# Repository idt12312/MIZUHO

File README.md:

# MIZUHOについて
## 概要
マイクロマウスの機体です。  

第37回全日本マイクロマウス大会のクラッシック競技フレッシュマンクラスに出場しました。  
予選を通過し、決勝では11位のタイムで完走しました。

## 使用部品

|          |                 |
|------------------|--------------------------|
| マイコン         | STM32F405RGT                |
| 6軸センサ        | MPU6500                  |
| モータドライバ   | DRV8835                  |
| フォトダイオード | SFH213FA                 |
| 赤外線LED        | VSLY5850                 |
| モーター         | Faulhaber 1717+IEH2-1024 |
| バッテリー       | Hyperion 1cel 120mA × 2  |

# 内容物
* pcb/ : kicadの基板データ
* firmware/ : stm32のファームウェア(eclipseのプロジェクトファイル)

# ファームウェアについて 
## 構成
↓の画像のような構成になっています。

[FreeRTOS](http://www.freertos.org/)を利用しています。  
上の画像の緑の色のついている部分がFreeRTOSのタスクになっています。  

## 制御の概要
だいたいこんな感じです。

## 探索アルゴリズム
[以前作ったもの](https://github.com/idt12312/MazeSolver2015)を使用しています。

# 回路について
[回路図はここからpdfダウンロードできます。](./doc/micromouse2016.pdf)

## 壁センサ
壁センサは少し工夫したので説明しておきます。  
ロ技研内での技術交流のために作成したまとめ文章も置いておくので、よかったら見てください  
[研究報告書](https://github.com/idt12312/MIZUHO/blob/master/doc/docment.pdf)  

外乱を防ぐために赤外線LEDを変調して使っています。

受光した信号は直交復調に基づいて復調しています。  
計算自体はDFTをとある周波数についてだけ計算することと同じです。  

受光した信号を

、サンプリング周波数を

とします。  
ここでは

から周波数

成分の強度を計算するとします。  

まず

を計算します。  

次に

の絶対値を計算することで  

に含まれる周波数

の振幅を得ることができます。

# 開発環境
## 基板
* 基板の外形はinventorで作成 -> dxfで出力
* 回路図・アートワークはKiCad 4.0.4-stableで作成

## STM32
* コンパイラ : GCC 4.9.3 (arm-none-eabi)
* デバッガ : GDB 7.8.0.20150604-cvs (arm-none-eabi)
* OpenOCD 0.9.0
* IDE : Eclipse
  * CDT
  * GNU ARM Eclipse plugin
* eclipseのプロジェクトの雛形はGNU ARM Eclipse pluginから自動生成されるものを使用
* STM32のStandard Peripheral Libraryを使用

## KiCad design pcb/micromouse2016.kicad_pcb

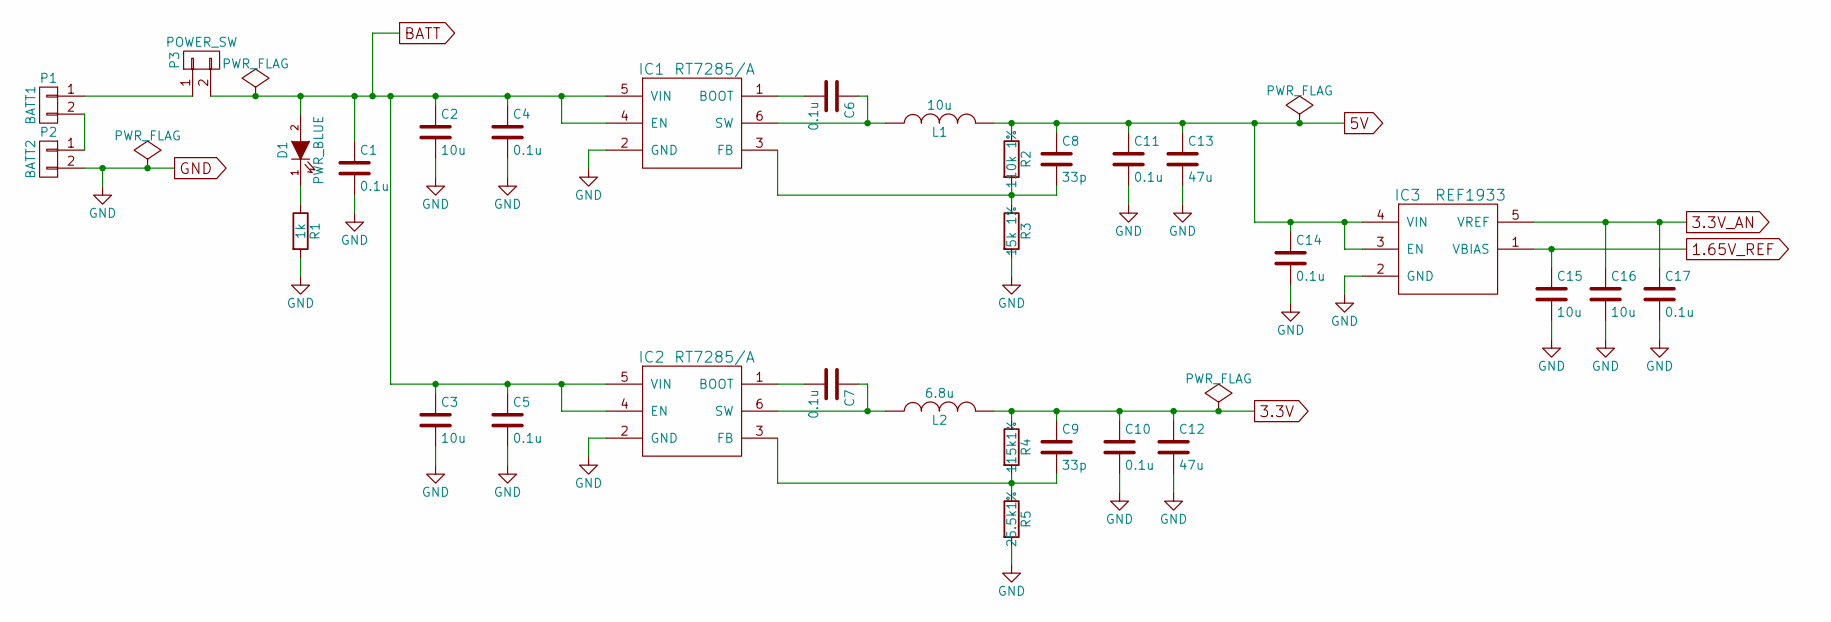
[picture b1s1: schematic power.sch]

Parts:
C1, C4, C5, C6, C7, C10, C11, C14, C17: 0.1u; C_0603
C2, C3, C15, C16: 10u; C_0603
C8, C9: 33p; C_0603
C12, C13: 47u; C_1206
D1: PWR_BLUE; LED_0805
IC1, IC2: RT7285/A; SOT-23-6
IC3: REF1933; SOT-23-5
L1: 10u; R_0805
L2: 6.8u; R_0805
P1: BATT1; JST_PH_B2B-PH-K_02x2.00mm_Straight
P2: BATT2; JST_PH_B2B-PH-K_02x2.00mm_Straight
P3: POWER_SW; Pin_Header_Straight_1x02
R1: 1k; R_0603
R2: 110k 1%; R_0603
R3: 15k 1%; R_0603
R4: 115k1%; R_0603
R5: 25.5k1%; R_0603

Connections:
1.65V_REF: C15.1, IC3.1 (VBIAS); also elsewhere on the board
3.3V: C9.1, C10.1, C12.1, L2.2, R4.1; also elsewhere on the board
3.3V_AN: C16.1, C17.1, IC3.5 (VREF); also elsewhere on the board
5V: C8.1, C11.1, C13.1, C14.1, IC3.3 (EN), IC3.4 (VIN), L1.2, R2.1; also elsewhere on the board
BATT: C1.1, C2.1, C3.1, C4.1, C5.1, D1.2 (A), IC1.4 (EN), IC1.5 (VIN), IC2.4 (EN), IC2.5 (VIN), P3.2; also elsewhere on the board
GND: C1.2, C2.2, C3.2, C4.2, C5.2, C10.2, C11.2, C12.2, C13.2, C14.2, C15.2, C16.2, C17.2, IC1.2 (GND), IC2.2 (GND), IC3.2 (GND), P2.2, R1.2, R3.2, R5.2; also elsewhere on the board
unnamed: C6.1, IC1.6 (SW), L1.1
unnamed: C6.2, IC1.1 (BOOT)
unnamed: C7.1, IC2.6 (SW), L2.1
unnamed: C7.2, IC2.1 (BOOT)
unnamed: C8.2, IC1.3 (FB), R2.2, R3.1
unnamed: C9.2, IC2.3 (FB), R4.2, R5.1
unnamed: D1.1 (K), R1.1
unnamed: P1.1, P3.1
unnamed: P1.2, P2.1

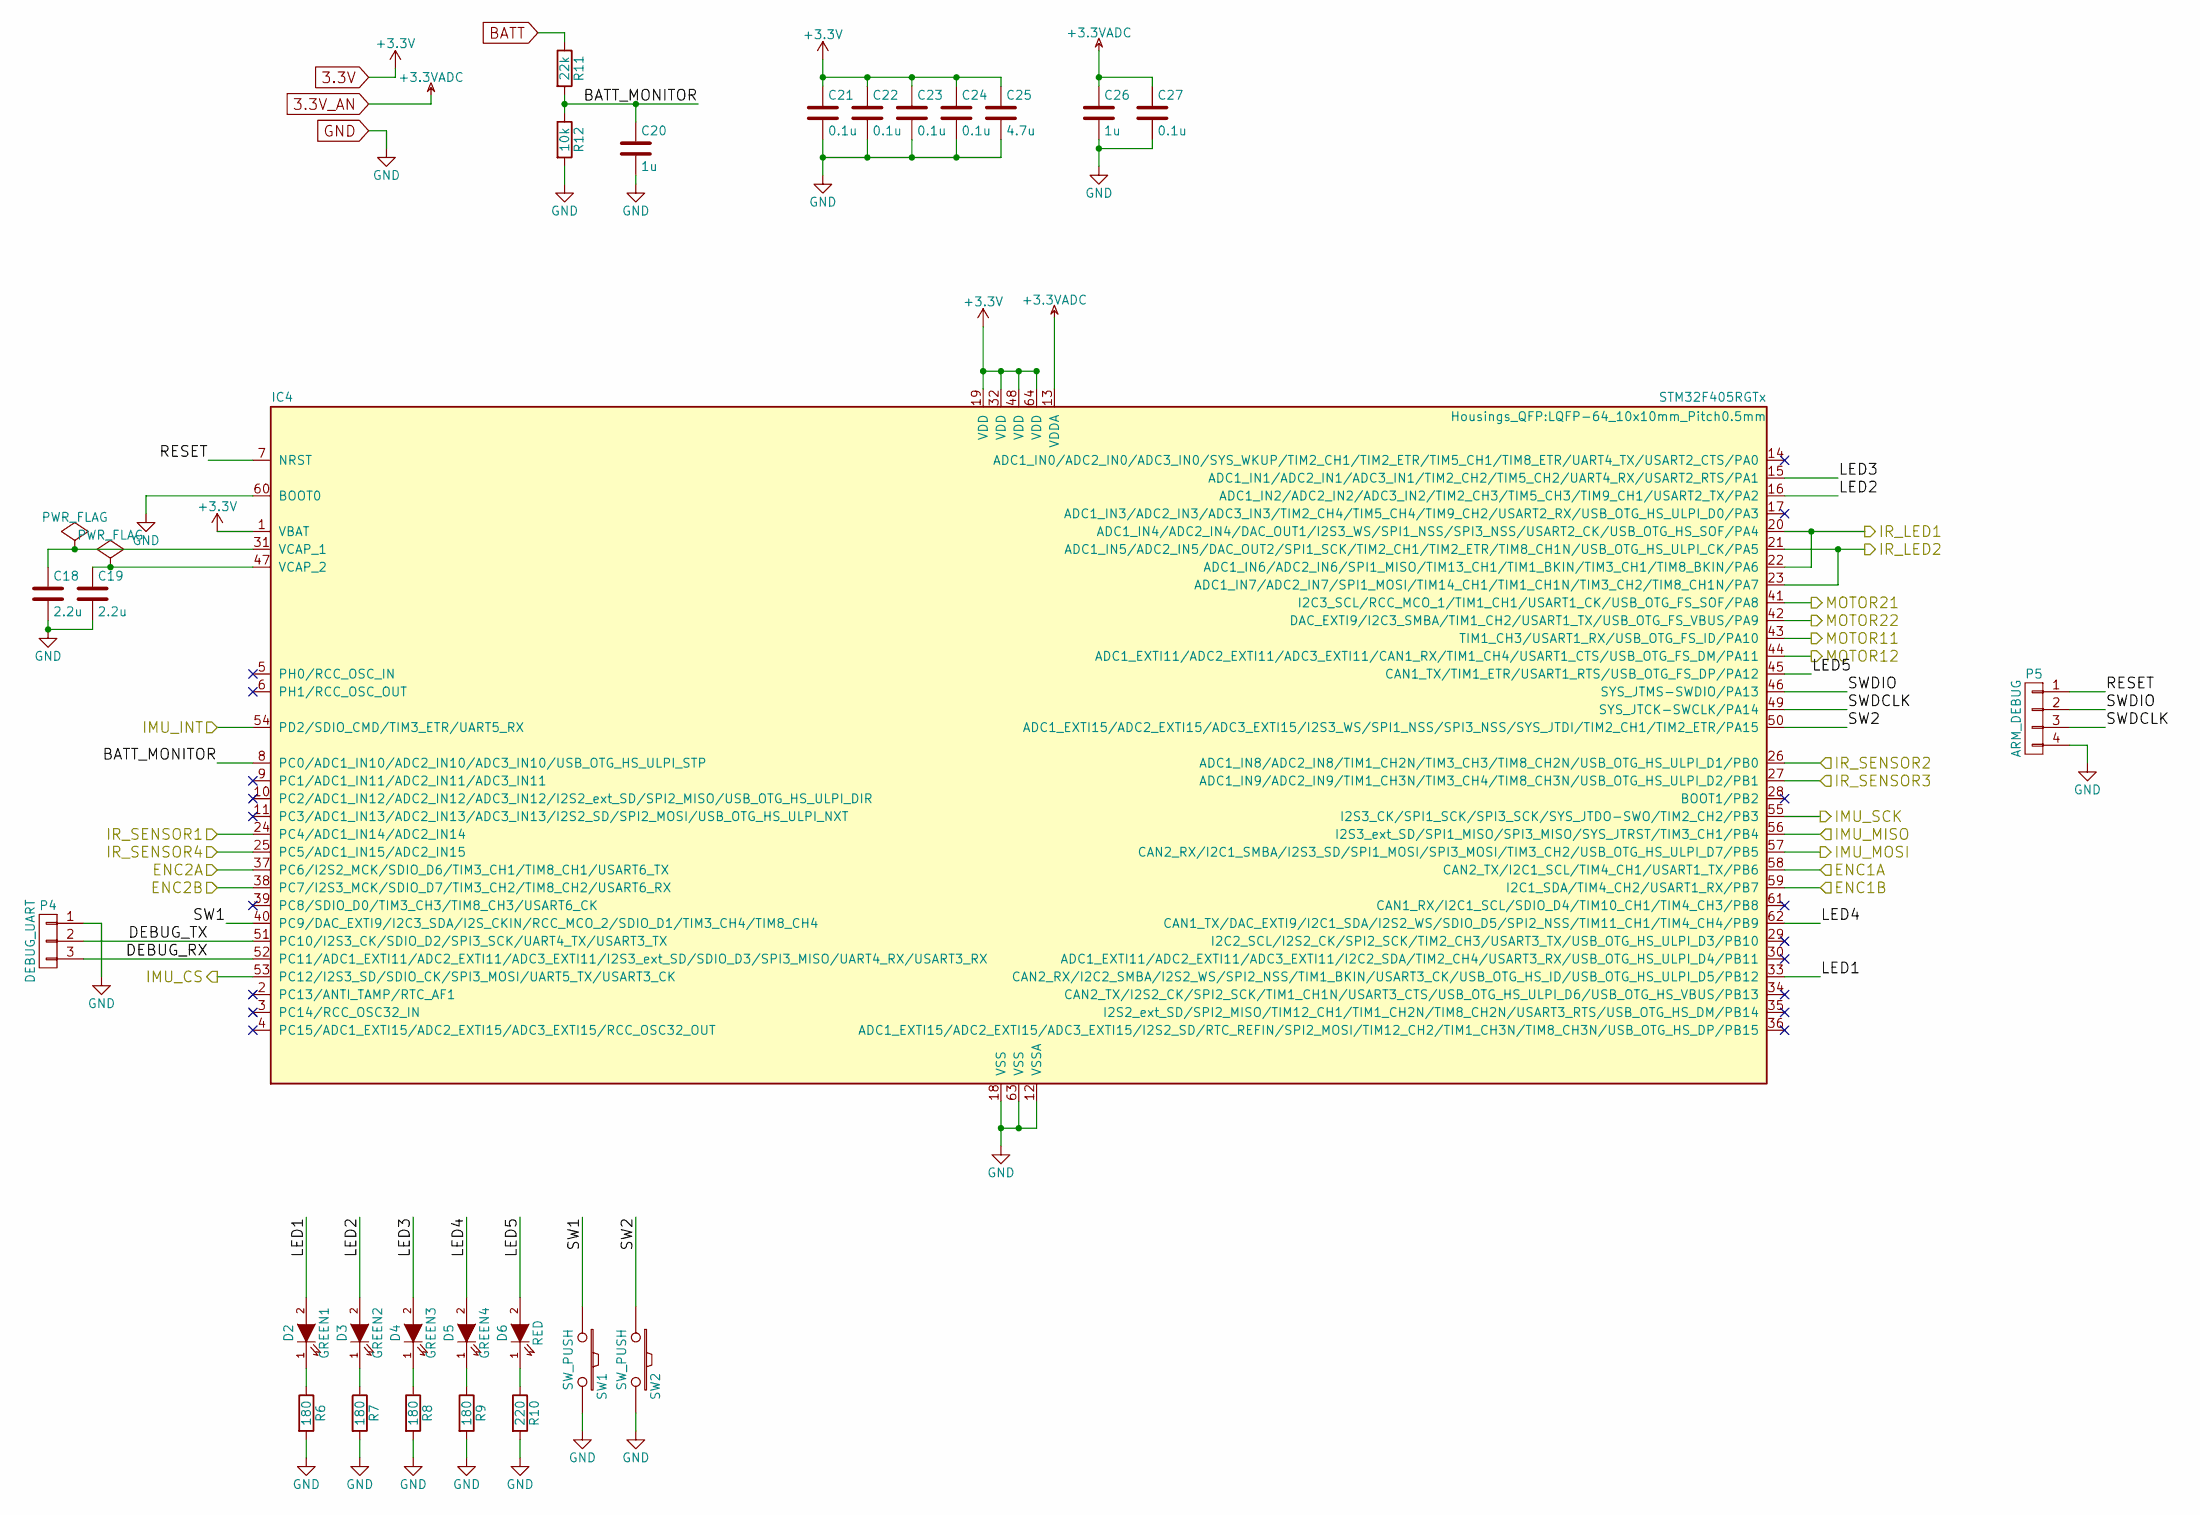
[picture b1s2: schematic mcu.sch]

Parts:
C18, C19: 2.2u; C_0603
C20, C26: 1u; C_0603
C21, C22, C23, C24, C27: 0.1u; C_0603
C25: 4.7u; C_0603
D2: GREEN1; LED_0805
D3: GREEN2; LED_0805
D4: GREEN3; LED_0805
D5: GREEN4; LED_0805
D6: RED; LED_0805
IC4: STM32F405RGTx; LQFP-64_10x10mm_Pitch0.5mm
P4: DEBUG_UART; Pin_Header_Straight_1x03
P5: ARM_DEBUG; Pin_Header_Straight_1x04
R6, R7, R8, R9: 180; R_0603
R10: 220; R_0603
R11: 22k; R_0603
R12: 10k; R_0603
SW1, SW2: SW_PUSH; SKRPACE010

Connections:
3.3V: C21.1, C22.1, C23.1, C24.1, C25.1, IC4.1 (VBAT), IC4.19 (VDD), IC4.32 (VDD), IC4.48 (VDD), IC4.64 (VDD); also elsewhere on the board
3.3V_AN: C26.1, C27.1, IC4.13 (VDDA); also elsewhere on the board
/imu/IMU_CS: IC4.53 (PC12/I2S3_SD/SDIO_CK/SPI3_MOSI/UART5_TX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); also elsewhere on the board
/imu/IMU_INT: IC4.54 (PD2/SDIO_CMD/TIM3_ETR/UART5_RX); also elsewhere on the board
/imu/IMU_MISO: IC4.56 (I2S3_ext_SD/SPI1_MISO/SPI3_MISO/SYS_JTR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); also elsewhere on the board
/imu/IMU_MOSI: IC4.57 (CAN2_RX/I2C1_SMBA/I2S3_SD/SPI1_MOSI/SPI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); also elsewhere on the board
/ir_transmitter1/IN: IC4.20 (ADC1_IN4/ADC2_IN4/DAC_OUT1/I2S3_WS/SPI1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), IC4.22 (ADC1_IN6/ADC2_IN6/SPI1_MISO/TIM13_CH1/T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); also elsewhere on the board
/ir_transmitter2/IN: IC4.21 (ADC1_IN5/ADC2_IN5/DAC_OUT2/SPI1_SCK/TIM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), IC4.23 (ADC1_IN7/ADC2_IN7/SPI1_MOSI/TIM14_CH1/T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); also elsewhere on the board
/mcu/BATT_MONITOR: C20.1, IC4.8 (PC0/ADC1_IN10/ADC2_IN10/ADC3_IN10/USB_O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), R11.2, R12.1
/mcu/DEBUG_RX: IC4.52 (PC11/ADC1_EXTI11/ADC2_EXTI11/ADC3_EXTI1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), P4.3
/mcu/DEBUG_TX: IC4.51 (PC10/I2S3_CK/SDIO_D2/SPI3_SCK/UART4_TX/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), P4.2
/mcu/ENC1A: IC4.58 (CAN2_TX/I2C1_SCL/TIM4_CH1/USART1_TX/PB6); also elsewhere on the board
/mcu/ENC1B: IC4.59 (I2C1_SDA/TIM4_CH2/USART1_RX/PB7); also elsewhere on the board
/mcu/ENC2A: IC4.37 (PC6/I2S2_MCK/SDIO_D6/TIM3_CH1/TIM8_CH1/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); also elsewhere on the board
/mcu/ENC2B: IC4.38 (PC7/I2S3_MCK/SDIO_D7/TIM3_CH2/TIM8_CH2/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); also elsewhere on the board
/mcu/IMU_SCK: IC4.55 (I2S3_CK/SPI1_SCK/SPI3_SCK/SYS_JTDO-SWO/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); also elsewhere on the board
/mcu/IR_SENSOR2: IC4.26 (ADC1_IN8/ADC2_IN8/TIM1_CH2N/TIM3_CH3/TI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); also elsewhere on the board
/mcu/IR_SENSOR3: IC4.27 (ADC1_IN9/ADC2_IN9/TIM1_CH3N/TIM3_CH4/TI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); also elsewhere on the board
/mcu/LED1: D2.2 (A), IC4.33 (CAN2_RX/I2C2_SMBA/I2S2_WS/SPI2_NSS/TIM1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)
/mcu/LED2: D3.2 (A), IC4.16 (ADC1_IN2/ADC2_IN2/ADC3_IN2/TIM2_CH3/TIM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)
/mcu/LED3: D4.2 (A), IC4.15 (ADC1_IN1/ADC2_IN1/ADC3_IN1/TIM2_CH2/TIM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)
/mcu/LED4: D5.2 (A), IC4.62 (CAN1_TX/DAC_EXTI9/I2C1_SDA/I2S2_WS/SDIO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)
/mcu/LED5: D6.2 (A), IC4.45 (CAN1_TX/TIM1_ETR/USART1_RTS/USB_OTG_FS_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)
/mcu/RESET: IC4.7 (NRST), P5.1
/mcu/SW1: IC4.40 (PC9/DAC_EXTI9/I2C3_SDA/I2S_CKIN/RCC_MCO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), SW1.1
/mcu/SW2: IC4.50 (ADC1_EXTI15/ADC2_EXTI15/ADC3_EXTI15/I2S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), SW2.1
/mcu/SWDCLK: IC4.49 (SYS_JTCK-SWCLK/PA14), P5.3
/mcu/SWDIO: IC4.46 (SYS_JTMS-SWDIO/PA13), P5.2
/motor1/IN1_PHASE: IC4.43 (TIM1_CH3/USART1_RX/USB_OTG_FS_ID/PA10); also elsewhere on the board
/motor1/IN2/ENABLE: IC4.44 (ADC1_EXTI11/ADC2_EXTI11/ADC3_EXTI11/CAN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); also elsewhere on the board
/motor2/IN1_PHASE: IC4.41 (I2C3_SCL/RCC_MCO_1/TIM1_CH1/USART1_CK/U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); also elsewhere on the board
/motor2/IN2/ENABLE: IC4.42 (DAC_EXTI9/I2C3_SMBA/TIM1_CH2/USART1_TX/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); also elsewhere on the board
BATT: R11.1; also elsewhere on the board
GND: C18.2, C19.2, C20.2, C21.2, C22.2, C23.2, C24.2, C25.2, C26.2, C27.2, IC4.12 (VSSA), IC4.18 (VSS), IC4.60 (BOOT0), IC4.63 (VSS), P4.1, P5.4, R6.2, R7.2, R8.2, R9.2, R10.2, R12.2, SW1.2, SW2.2; also elsewhere on the board
unnamed: C18.1, IC4.31 (VCAP_1)
unnamed: C19.1, IC4.47 (VCAP_2)
unnamed: D2.1 (K), R6.1
unnamed: D3.1 (K), R7.1
unnamed: D4.1 (K), R8.1
unnamed: D5.1 (K), R9.1
unnamed: D6.1 (K), R10.1

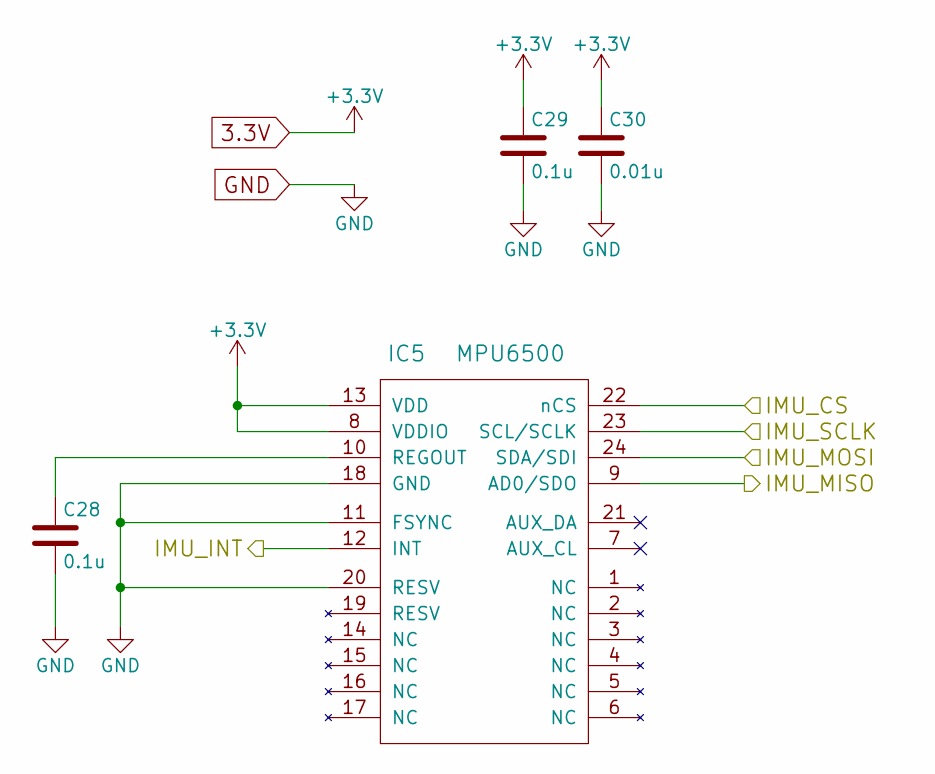
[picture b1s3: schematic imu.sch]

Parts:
C28, C29: 0.1u; C_0603
C30: 0.01u; C_0603
IC5: MPU6500; QFN-24-1EP_3x3mm_Pitch0.4mm_HandSolder

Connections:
3.3V: C29.1, C30.1, IC5.8 (VDDIO), IC5.13 (VDD); also elsewhere on the board
/imu/IMU_CS: IC5.22 (nCS); also elsewhere on the board
/imu/IMU_INT: IC5.12 (INT); also elsewhere on the board
/imu/IMU_MISO: IC5.9 (AD0/SDO); also elsewhere on the board
/imu/IMU_MOSI: IC5.24 (SDA/SDI); also elsewhere on the board
/mcu/IMU_SCK: IC5.23 (SCL/SCLK); also elsewhere on the board
GND: C28.2, C29.2, C30.2, IC5.11 (FSYNC), IC5.18 (GND), IC5.20 (RESV); also elsewhere on the board
unnamed: C28.1, IC5.10 (REGOUT)

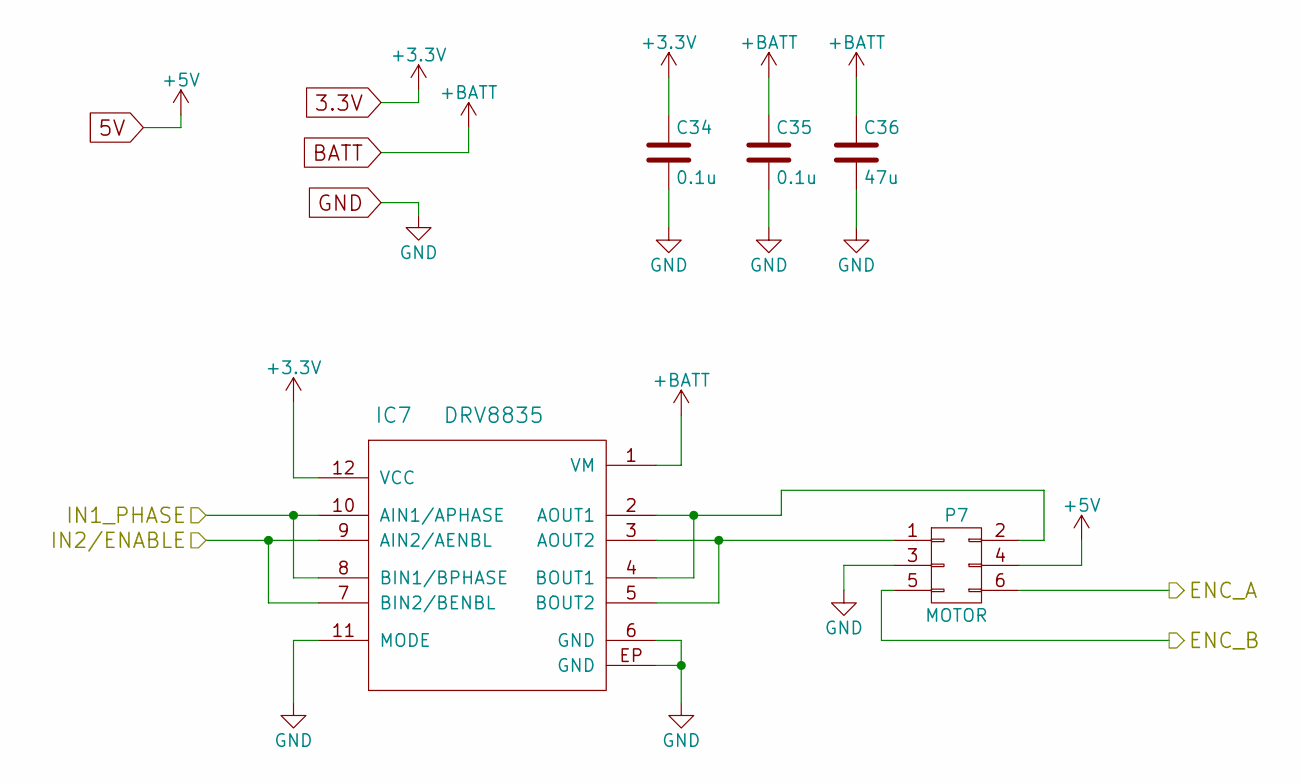
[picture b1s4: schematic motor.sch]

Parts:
C31, C32: 0.1u; C_0603
C33: 47u; C_1206
IC6: DRV8835
P6: MOTOR; Pin_Header_Straight_2x03

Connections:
3.3V: C31.1, IC6.12 (VCC); also elsewhere on the board
5V: P6.4; also elsewhere on the board
/mcu/ENC1A: P6.6; also elsewhere on the board
/mcu/ENC1B: P6.5; also elsewhere on the board
/motor1/IN1_PHASE: IC6.8 (BIN1/BPHASE), IC6.10 (AIN1/APHASE); also elsewhere on the board
/motor1/IN2/ENABLE: IC6.7 (BIN2/BENBL), IC6.9 (AIN2/AENBL); also elsewhere on the board
BATT: C32.1, C33.1, IC6.1 (VM); also elsewhere on the board
GND: C31.2, C32.2, C33.2, IC6.6 (GND), IC6.11 (MODE), IC6.EP (GND), P6.3; also elsewhere on the board
unnamed: IC6.2 (AOUT1), IC6.4 (BOUT1), P6.2
unnamed: IC6.3 (AOUT2), IC6.5 (BOUT2), P6.1

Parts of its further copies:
C34, C35: 0.1u; C_0603
C36: 47u; C_1206
IC7: DRV8835
P7: MOTOR; Pin_Header_Straight_2x03

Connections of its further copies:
3.3V: C34.1, IC7.12 (VCC); also elsewhere on the board
5V: P7.4; also elsewhere on the board
/mcu/ENC2A: P7.6; also elsewhere on the board
/mcu/ENC2B: P7.5; also elsewhere on the board
/motor2/IN1_PHASE: IC7.8 (BIN1/BPHASE), IC7.10 (AIN1/APHASE); also elsewhere on the board
/motor2/IN2/ENABLE: IC7.7 (BIN2/BENBL), IC7.9 (AIN2/AENBL); also elsewhere on the board
BATT: C35.1, C36.1, IC7.1 (VM); also elsewhere on the board
GND: C34.2, C35.2, C36.2, IC7.6 (GND), IC7.11 (MODE), IC7.EP (GND), P7.3; also elsewhere on the board
unnamed: IC7.2 (AOUT1), IC7.4 (BOUT1), P7.2
unnamed: IC7.3 (AOUT2), IC7.5 (BOUT2), P7.1

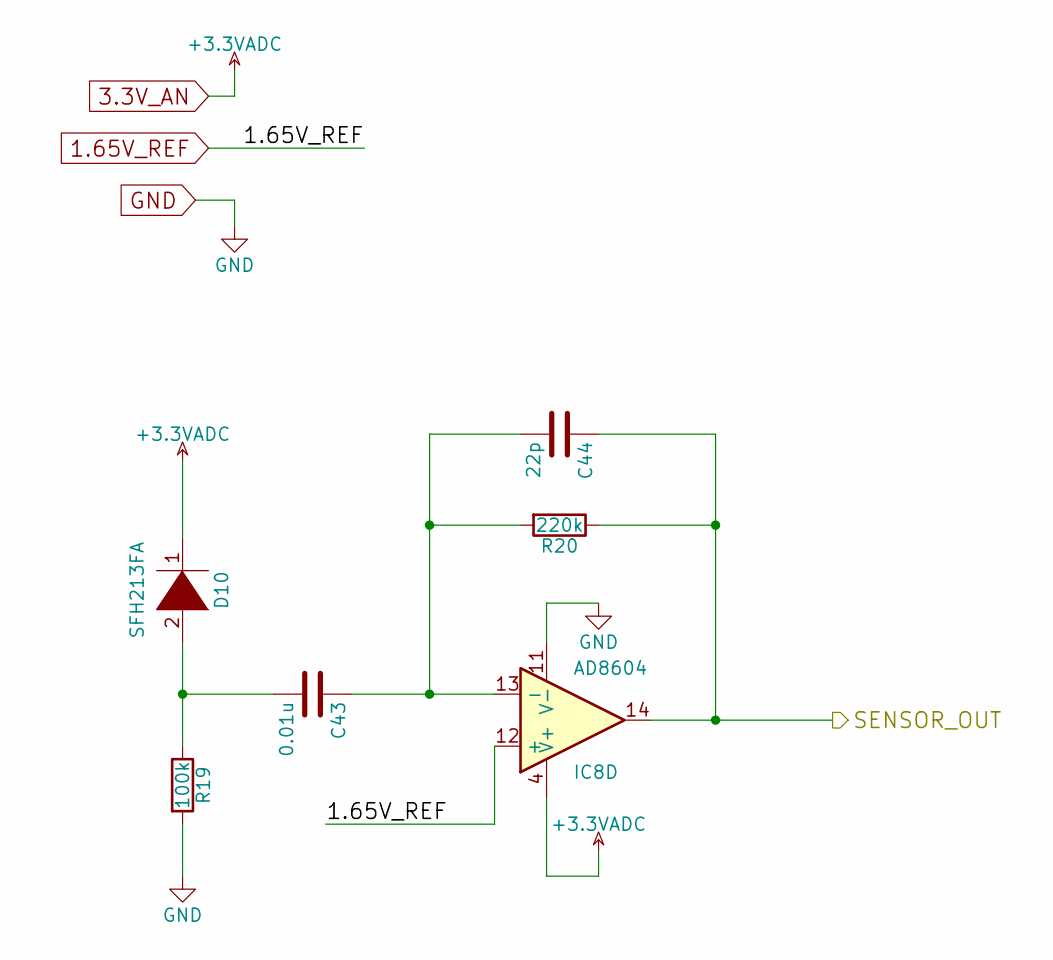
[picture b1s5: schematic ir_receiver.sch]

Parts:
C37: 0.01u; C_0603
C38: 22p; C_0603
D7: SFH213FA; LED_5mm_angle
IC8: AD8604; TSSOP-14_4.4x5mm_Pitch0.65mm
R13: 100k; R_0603
R14: 220k; R_0603

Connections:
1.65V_REF: IC8.3 (+), IC8.5 (+), IC8.10 (+), IC8.12 (+); also elsewhere on the board
3.3V_AN: D7.1 (K), IC8.4 (V+); also elsewhere on the board
/mcu/IR_SENSOR2: IC8.7; also elsewhere on the board
/mcu/IR_SENSOR3: IC8.8; also elsewhere on the board
GND: IC8.11 (V-), R13.2; also elsewhere on the board
unnamed: C37.2, D7.2 (A), R13.1
unnamed 46: IC8.6 (-); also elsewhere on the board
unnamed 48: IC8.9 (-); also elsewhere on the board

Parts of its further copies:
C39, C41, C43: 0.01u; C_0603
C40, C42, C44: 22p; C_0603
D8, D9, D10: SFH213FA; LED_5mm_angle
R15, R17, R19: 100k; R_0603
R16, R18, R20: 220k; R_0603

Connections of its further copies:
3.3V_AN: D8.1 (K), D9.1 (K), D10.1 (K); also elsewhere on the board
/mcu/IR_SENSOR2: C40.1, R16.1; also elsewhere on the board
/mcu/IR_SENSOR3: C42.1, R18.1; also elsewhere on the board
GND: R15.2, R17.2, R19.2; also elsewhere on the board
unnamed 46: C39.1, C40.2, R16.2; also elsewhere on the board
unnamed: C39.2, D8.2 (A), R15.1
unnamed 48: C41.1, C42.2, R18.2; also elsewhere on the board
unnamed: C41.2, D9.2 (A), R17.1
unnamed: C43.2, D10.2 (A), R19.1

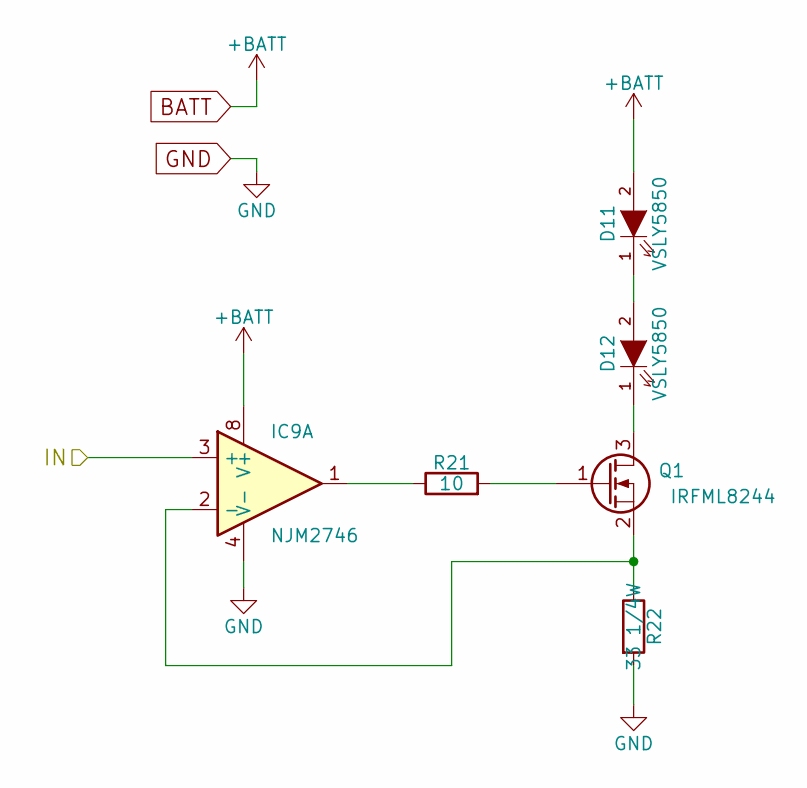
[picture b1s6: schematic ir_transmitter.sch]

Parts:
D11, D12: VSLY5850; LED_5mm_angle
IC9: NJM2746; TSSOP-8_4.4x3mm_Pitch0.65mm
Q1: IRFML8244; SOT-23
R21: 10; R_0603
R22: 33 1/4W; R_1206

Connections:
/ir_transmitter1/IN: IC9.3 (+); also elsewhere on the board
/ir_transmitter2/IN: IC9.5 (+); also elsewhere on the board
BATT: D11.2 (A), IC9.8 (V+); also elsewhere on the board
GND: IC9.4 (V-), R22.2; also elsewhere on the board
unnamed: D11.1 (K), D12.2 (A)
unnamed: D12.1 (K), Q1.3 (D)
unnamed: IC9.1, R21.1
unnamed: IC9.2 (-), Q1.2 (S), R22.1
unnamed 67: IC9.6 (-); also elsewhere on the board
unnamed 68: IC9.7; also elsewhere on the board
unnamed: Q1.1 (G), R21.2

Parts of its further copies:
D13, D14: VSLY5850; LED_5mm_angle
Q2: IRFML8244; SOT-23
R23: 10; R_0603

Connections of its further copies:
BATT: D13.2 (A); also elsewhere on the board
unnamed: D13.1 (K), D14.2 (A)
unnamed: D14.1 (K), Q2.3 (D)
unnamed 67: Q2.2 (S); also elsewhere on the board
unnamed 68: R23.1; also elsewhere on the board
unnamed: Q2.1 (G), R23.2

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
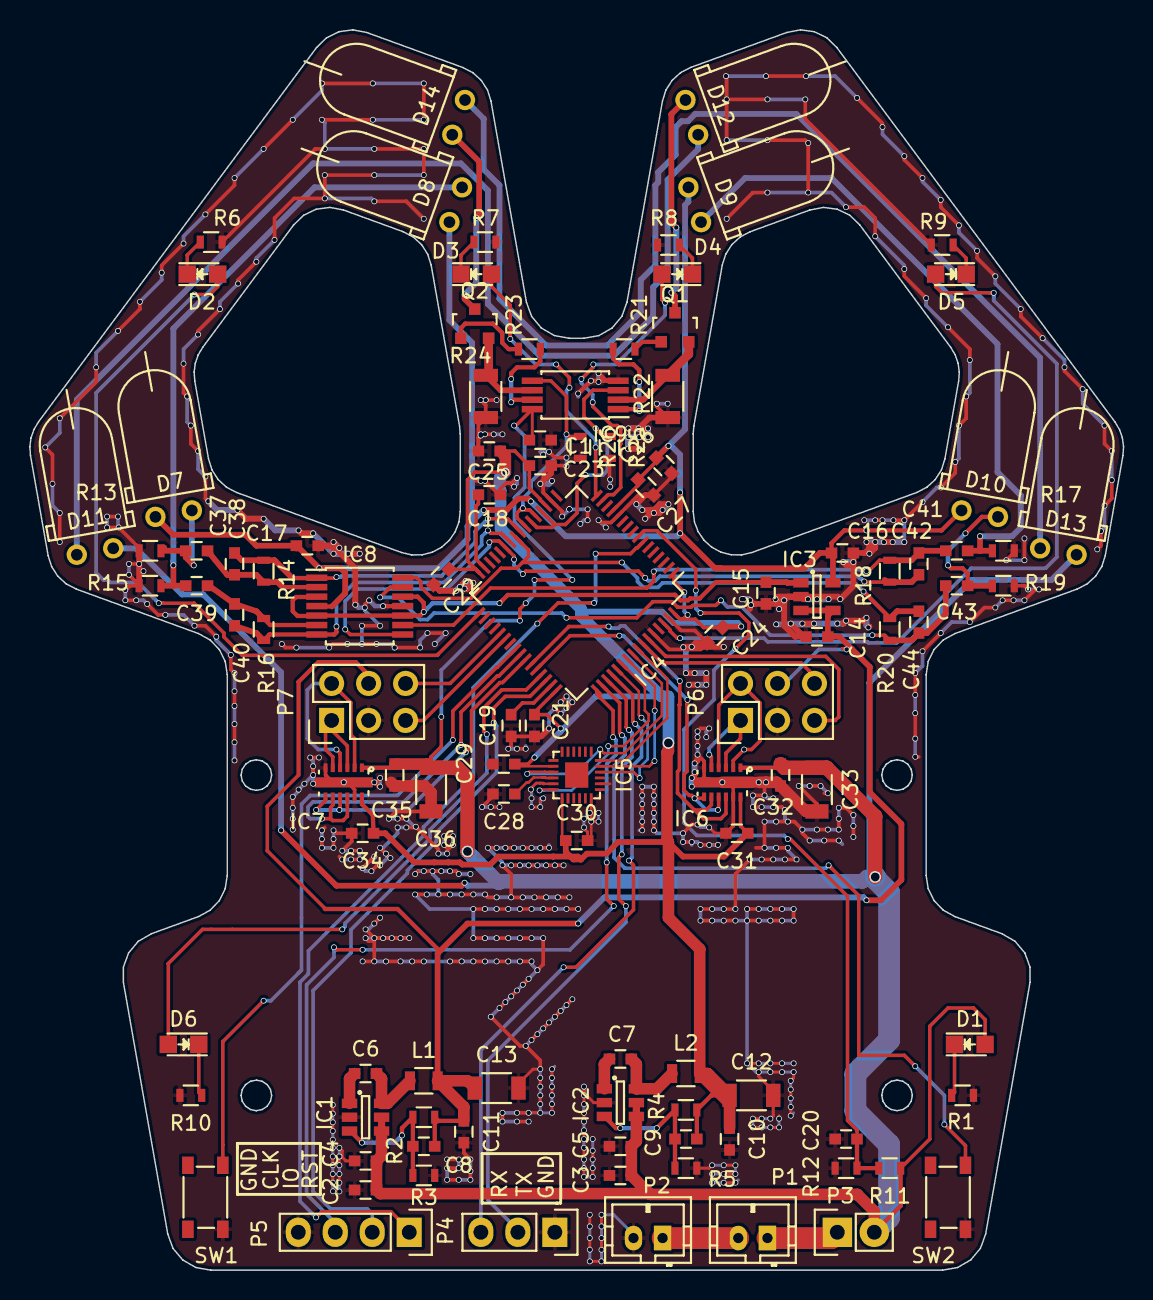
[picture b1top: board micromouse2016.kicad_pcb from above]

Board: 2 copper layers, 75.1 x 85.2 mm, 106 parts (0 on the bottom side), 77 nets.

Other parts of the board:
R24: 15 1/4W; R_1206
R25, R26: 10k; R_0603

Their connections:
/ir_transmitter1/IN: R25.1; also elsewhere on the board
/ir_transmitter2/IN: R26.1; also elsewhere on the board
GND: R24.2, R25.2, R26.2; also elsewhere on the board
unnamed 67: R24.1; also elsewhere on the board

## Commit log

2016-09-29 基板データを追加
2016-09-29 eclipseのプロジェクトを作成
2016-09-29 FPU・内部発振を有効化
2016-10-02 UART(DMA使用)を扱う部分を実装
2016-10-02 ロータリエンコーダの読み取り部分を実装
2016-10-02 モータ用PWMの操作部分を実装
2016-10-02 MPU6500とSPIを実装 Z軸周りの角加速度だけ取得できる
2016-10-02 ヘッダをincludeに移動
2016-10-02 READMEを追加
2016-10-22 MPU6500周りを修正 ・CSの操作 ・MPU6500のレジスタのアドレスの指定方法 ・MPU6500から読み取った角速度データの解釈の仕方
2016-10-22 Tickを実装
2016-10-25 エンコーダの読み取り部分を修正
2016-10-25 LEDとボタンの操作部分を実装
2016-10-25 モータの操作部分を実装
2016-10-25 標準出力をUARTに流すように修正
2016-10-25 バッテリー電圧計測部分を実装
2016-10-25 赤外線の発光受光部分を実装
2016-10-25 各機能のテスト
2016-10-25 ソースのディレクトリを変更
2016-10-25 FreeRTOSを導入 MPU6500の初期化時にTick_waitを使っているが、RTOSを起動するまで使えないのでfor分で待つように変更
2016-10-28 CMSISのヘッダを最新版に差し替え & DSPライブラリを追加
2016-10-29 直交復調を実装
2016-10-29 C++のコンパイルオプションでRTTIと例外を無効化
2016-10-29 赤外線LED用のLEDの設定が間違っていたので修正 ・PWM周波数が2倍になっていたので修正 ・DMAの半分送信割り込みが起こったとき、点滅させるLEDを切り替え忘れていたので修正
2016-10-29 直交復調のテスト
2016-11-01 ジャイロセンサのオフセットのキャリブレーションを実装
2016-11-03 SPI通信部分を分離し、DMAを使った実装にした DMAの転送が終了するまではセマフォを使ってブロックできる
2016-11-03 割り込み優先度を調整
2016-11-03 QuadratureDemodulatorを修正 ・計算結果用のクラスを作ってそれを返すようにした ・回転因子をunique_ptrで実装
2016-11-03 バッテリー監視タスクを実装 バッテリー監視用ADCの設定を変更
2016-11-03 壁センサのためにサンプリングしている時、セマフォでブロックする実装に変更
2016-11-03 壁のあるなしを判定するタスクを実装
2016-11-03 エンコーダのデータのやり取りを構造体を通して行うように変更
2016-11-03 モータ入力を電圧で指定できるようにした
2016-11-03 モータの制御タスクを実装 ・車体の並進速度・角速度を目標値として与える ・モータにかける電圧(duty比)が制御入力
2016-11-07 起動直後にバッテリー電圧を計測してバッテリーの残量を判定するのをやめた コンデンサに充電しきる前に計測されてしまい、低く出てしまうから
2016-11-07 オドメトリを実装 & 動作確認
2016-11-09 PIDコントローラのAPIを変更
2016-11-09 ジャイロのオフセットキャリブレーションを修正
2016-11-09 Velocityの足し算引き算を実装
2016-11-09 軌道の生成部分を実装 テスト用に直進と超信地旋回を実装
2016-11-09 タイヤ径とドレッド径を実測により調整
2016-11-09 座標の取り方を変えた ・ロボット(ローカル)座標系は進行方向がy座標 ・ワールド座標系のx軸 -> ロボット座標系のx軸の角度がθ
2016-11-09 軌道追従コントローラを実装
2016-11-09 軌道追従制御のタスクを実装 直進・超信地旋回ができることを確認
2016-11-11 スラロームを実装
2016-11-11 C++の動的リンクを使わない設定を追加
2016-11-11 複数のTrajectoryを連続して実行できるように修正 Trajectoryをqueueから取り出すごとにodometoryをリセットしている
2016-11-11 直進、超信地旋回、スラローム旋回、それぞれ移動量などをパラメータで与えられるように修正
2016-11-11 Trajectoryを切り替えるごとに今いる位置の分だけあらかじめカウンタを進めるように修正 目標点を超えた状態でTrajectoryを切り替えると逆方向に戻ろうとしてしまうため
2016-11-12 角度の計測のみにgyroを使い、機体の速度制御はエンコーダの情報のみを用いる gyroから得た角速度情報を機体の速度制御に用いると振動的になるため
2016-11-12 軌道の追従制御において、あらかじめ計画した目標速度のフィードフォワード入力のゲインを設定できるようにした スラロームの際に大回りになってしまうため
2016-11-12 軌道追従の制御のパラメータをチューニング
2016-11-13 前壁センサの判定に使う閾値を左右に壁があるときとないときで変えられるように修正
2016-11-13 直進時に左右の壁を使ってx座標を修正する機能を追加
2016-11-13 機体の角度を計算をジャイロから得た角速度を使うかエンコーダから得た角速度を使うかを切り替えられるようにした 普段はジャイロを使うが、タイヤを浮かせてデバッグするときにはエンコーダを使うといい
2016-11-13 1つのTrajectoryが終了したときの処理の追加
2016-11-13 バックをする時は目標点のx座標を追従するために入力する角速度の方向を逆にした
2016-11-14 バックしてマシンの尻を壁に当てて補正するのを実装 Trajectoryのset_adjust_odometry_flagをたてるとそのTrajectoryを実行後に座標(y,theta)をリセットする
2016-11-14 Trajectory -> Motion にrename
2016-11-14 デバッグのための設定を追加
2016-11-14 モータコントローラ、軌道追従制御コントローラの制御パラメータはコンストラクタの引数で渡すのではなく、 コンストラクタに直接うめこむ実装に変更
2016-11-14 クラスの宣言と実装を分けた
2016-11-14 ソースディレクトリを整理
2016-11-16 各タスクをクラスにまとめた & motionが切り替わる時のodometoryのリセット処理を修正
2016-11-16 SPIの通信速度を切り替えられるようにし、初期設定は低速、データの読み取りは高速に通信するように変更
2016-11-16 ボタンを監視するタスクを追加
2016-11-16 ロボットの機械的なパラメータの名前を変更
2016-11-16 ・壁の判定を少し手前で行うように変更 ・壁当て補正を修正 ・区画が切り替わる時の目標値との誤差の計算を修正 ・Motionの終了通知
2016-11-16 ジャイロのゲインを変更
2016-11-16 超信地旋回の角速度のフィードフォワードのゲインを設定できるようにした
2016-11-16 探索アルゴリズムをsubmoduleとして取り込んだ
2016-11-16 ビルド設定に探索ライブラリを追加
2016-11-17 コンパイルオプションを追加
2016-11-17 タスクのスタックを調整
2016-11-17 PIDControllerとOdometryにおける微分のための前回値のリセット処理を追加
2016-11-17 Motion周りの終わりの処理を修正
2016-11-17 区画の終了判定を修正
2016-11-17 探索部分を実装 各種パラメータを調整
2016-11-17 Motionにパラメータとして与えられるようにした
2016-11-17 最速走行の動作を実装 ・最短走行と探索走行で走行パラメータをわけた ・手をかざすとスタートする ・LEDを制御
2016-11-18 LEDの点滅タスクを点滅パターンをいろいろいじれるように修正
2016-11-18 横壁補正を実装
2016-11-18 スタートするための操作をいろいろ実装 手をかざすとスタートする
2016-11-18 パラメータを調整
2016-11-18 片側にしか壁がない時は壁の補正をしない
2016-11-18 最速走行まわりのバグを修正
2016-11-19 gitignoreを追加
2016-11-22 軌道をプロットするMATLABスクリプトを追加
2016-11-24 回路図を修正 ・赤外線LEDの発光回路にpull down抵抗を追加 ・赤外線LEDの発光回路の電流制限抵抗の値を変更
2016-11-27 実体配線図に抵抗を追加
2016-12-10 READMEを追記
2017-02-28 README.mdの数式をcodecogsで生成した画像で表示するようにした
2017-02-28 README.mdの数式で、inlineのものはinline指定にした
2017-02-28 README.mdの数式へのリンクをmarkdown形式で書いた
2017-02-28 Revert "README.mdの数式へのリンクをmarkdown形式で書いた"
    This reverts commit 1478dd8bda064d6265e28aa823ffcd6b57f4bd83.
2019-02-09 壁センサに関するまとめ文章を追加
